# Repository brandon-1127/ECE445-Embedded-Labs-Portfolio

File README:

Hello!

This is a portfolio of all my embedded labs for ECE445 at UT Austin. They range from speakers to alarm clocks to my final project(a glove controlled wirless robotic arm).

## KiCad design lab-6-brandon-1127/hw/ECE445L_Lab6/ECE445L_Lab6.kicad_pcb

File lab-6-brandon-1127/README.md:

## 0 Repository Structure

The typical explanation for the repo structure. Lab specific instructions can be
found further below.

### 0.1 HW

The `hw` folder should contain your schematic and board files for your PCB or
circuits. In labs 1-5 and 10, you will be creating schematics for your circuit
in KiCad.

### 0.2 SW

The `sw` folder should contain your application firmware and software written
for the lab. The `sw/inc` folder contains firmware drivers written for you by
Professor Valvano. Feel free to write your own (in fact, in some labs, you may
be required to write your own).

You can place any other source files in the `sw` folder. TAs will look at the
files you create and/or modify for software quality and for running your
project.

### 0.3 Resources

A couple files are provided in the Resources folder so you don't have to keep
searching for that one TI document. Some of them are immediately useful, like
the TM4C datasheet. Others may be useful for your final project, like the
TM4C_System_Design_Guidelines page.

### 0.4 Git and Github

We will extensively use Git and Github for managing lab projects. This makes it
easier for TAs to grade and help debug the project by allowing us to see commit
histories, maintain a common project structure, and likewise, it makes it easier
for students to collaborate with partners, merge different codebases, and to
debug their work by having a history of commits.

Two common ways of using Git and Github are [Github Desktop](https://desktop.github.com/) and the [command line](https://git-scm.com/downloads).
[Tutorials](https://dev.to/mollynem/git-github--workflow-fundamentals-5496) are also abundant on the net for you to peruse. We've provided a cheatsheet for git
in the Resources folder.

It is highly recommended to make the most out of Git, even if you've never used
it before. Version control will save you a lot of suffering, and tools like Git
or SVN are ubiquitous in the industry.

A gitignore file is added to the root of this repo that may prevent specific
files from being tagged to the repo. This are typically autogenerated output
files we don't care about, but sometimes other stuff (like .lib files) falls
through that we want. Feel free to modify if necessary.

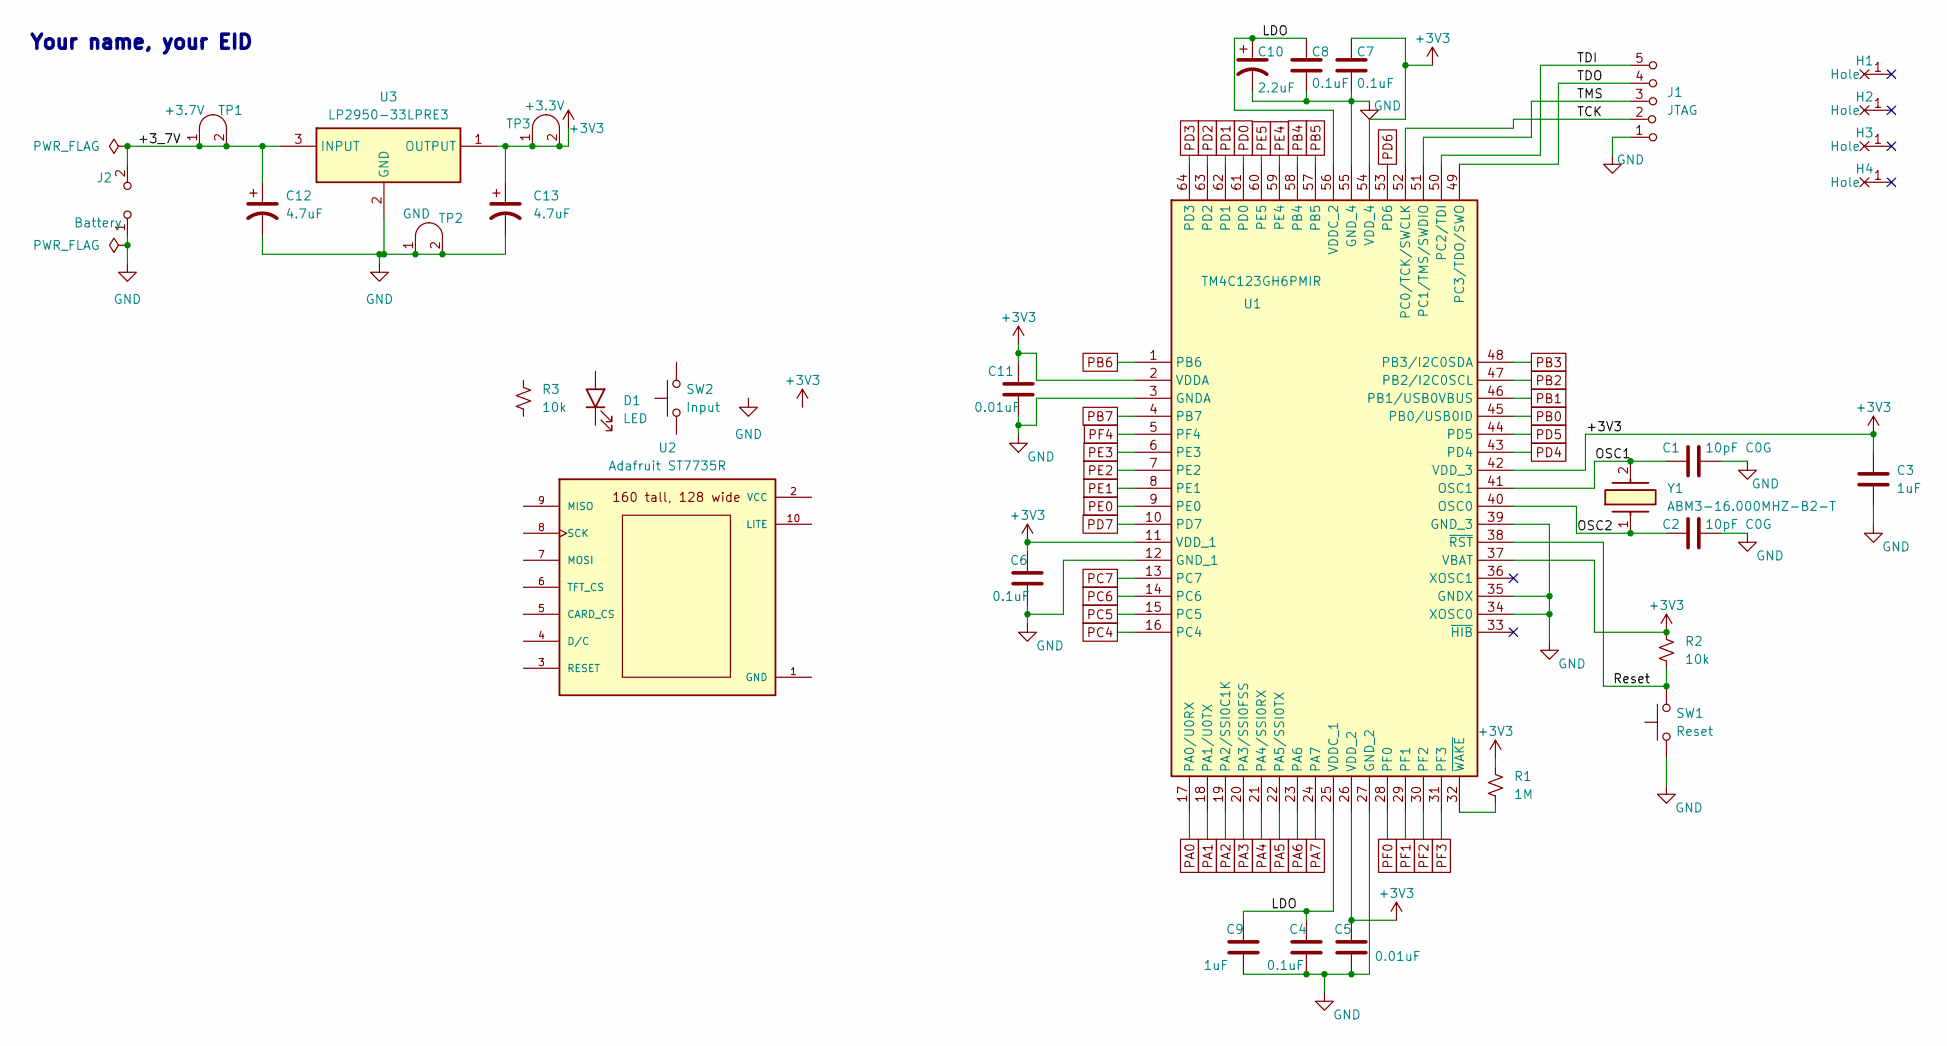
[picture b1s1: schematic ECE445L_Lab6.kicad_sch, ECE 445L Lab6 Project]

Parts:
C1, C2: 10pF C0G; C_Axial_200mil
C3, C9: 1uF; C_Axial_200mil
C4, C6, C7, C8: 0.1uF; C_Axial_200mil
C5, C11: 0.01uF; C_Axial_200mil
C10: 2.2uF; CP_Radial_Tantal200mil
C12, C13: 4.7uF; CP_Radial_Tantal200mil
D1: LED; LED_D5.0mm
H1, H2, H3, H4: MountingHole_4_40
J1: JTAG; PinHeader_1x05_P2.54mm_Vertical
J2: Battery; PinHeader_1x02_P2.54mm_Vertical
R1: 1M; R_Axial_DIN0204_L3.6mm_D1.6mm_P7.62mm_Horizontal
R2, R3: 10k; R_Axial_DIN0204_L3.6mm_D1.6mm_P7.62mm_Horizontal
SW1: Reset; SW_PUSH_6mm
SW2: Input; SW_PUSH_6mm
TP1: +3.7V; Testpoint_1x02_P2.54mm
TP2: GND; Testpoint_1x02_P2.54mm
TP3: +3.3V; Testpoint_1x02_P2.54mm
U1: TM4C123GH6PMIR; QFP50P1200X1200X160-64N; Mouser Part Number 595-TM4C123GH6PMIR
U2: Adafruit ST7735R; adafruit_st7735r2
U3: LP2950-33LPRE3; TL431CLPM; Mouser Part Number 595-LP2950-33LPRE3
Y1: ABM3-16.000MHZ-B2-T; ABM3; Mouser Part Number 815-ABM3-16-B2-T

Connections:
+3V3: C3.1, C5.1, C6.1, C7.1, C11.1, C13.1, R1.1, R2.1, TP3.1 (A), TP3.2 (B), U1.2 (VDDA), U1.11 (VDD_1), U1.26 (VDD_2), U1.37 (VBAT), U1.42 (VDD_3), U1.54 (VDD_4), U3.1 (OUTPUT)
/+3_7V: C12.1, J2.2 (B), TP1.1 (A), TP1.2 (B), U3.3 (INPUT)
/LDO: C4.1, C8.1, C9.1, C10.1, U1.25 (VDDC_1), U1.56 (VDDC_2)
/OSC1: C1.1, U1.41 (OSC1), Y1.2
/OSC2: C2.1, U1.40 (OSC0), Y1.1
/Reset: R2.2, SW1.2, U1.38 (~RST)
/TCK: J1.2 (B), U1.52 (PC0/TCK/SWCLK)
/TDI: J1.5 (C), U1.50 (PC2/TDI)
/TDO: J1.4 (C), U1.49 (PC3/TDO/SWO)
/TMS: J1.3 (C), U1.51 (PC1/TMS/SWDIO)
GND: C1.2, C2.2, C3.2, C4.2, C5.2, C6.2, C7.2, C8.2, C9.2, C10.2, C11.2, C12.2, C13.2, J1.1 (A), J2.1 (A), SW1.1, TP2.1 (A), TP2.2 (B), U1.3 (GNDA), U1.12 (GND_1), U1.27 (GND_2), U1.34 (XOSC0), U1.35 (GNDX), U1.39 (GND_3), U1.55 (GND_4), U3.2 (GND)
unnamed: R1.2, U1.32 (~WAKE)
PA0: U1.17 (PA0/U0RX)
PA1: U1.18 (PA1/U0TX)
PA2: U1.19 (PA2/SSI0C1K)
PA3: U1.20 (PA3/SSI0FSS)
PA4: U1.21 (PA4/SSI0RX)
PA5: U1.22 (PA5/SSI0TX)
PA6: U1.23 (PA6)
PA7: U1.24 (PA7)
PB0: U1.45 (PB0/USB0ID)
PB1: U1.46 (PB1/USB0VBUS)
PB2: U1.47 (PB2/I2C0SCL)
PB3: U1.48 (PB3/I2C0SDA)
PB4: U1.58 (PB4)
PB5: U1.57 (PB5)
PB6: U1.1 (PB6)
PB7: U1.4 (PB7)
PC4: U1.16 (PC4)
PC5: U1.15 (PC5)
PC6: U1.14 (PC6)
PC7: U1.13 (PC7)
PD0: U1.61 (PD0)
PD1: U1.62 (PD1)
PD2: U1.63 (PD2)
PD3: U1.64 (PD3)
PD4: U1.43 (PD4)
PD5: U1.44 (PD5)
PD6: U1.53 (PD6)
PD7: U1.10 (PD7)
PE0: U1.9 (PE0)
PE1: U1.8 (PE1)
PE2: U1.7 (PE2)
PE3: U1.6 (PE3)
PE4: U1.59 (PE4)
PE5: U1.60 (PE5)
PF0: U1.28 (PF0)
PF1: U1.29 (PF1)
PF2: U1.30 (PF2)
PF3: U1.31 (PF3)
PF4: U1.5 (PF4)

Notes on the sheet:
Your name, your EID

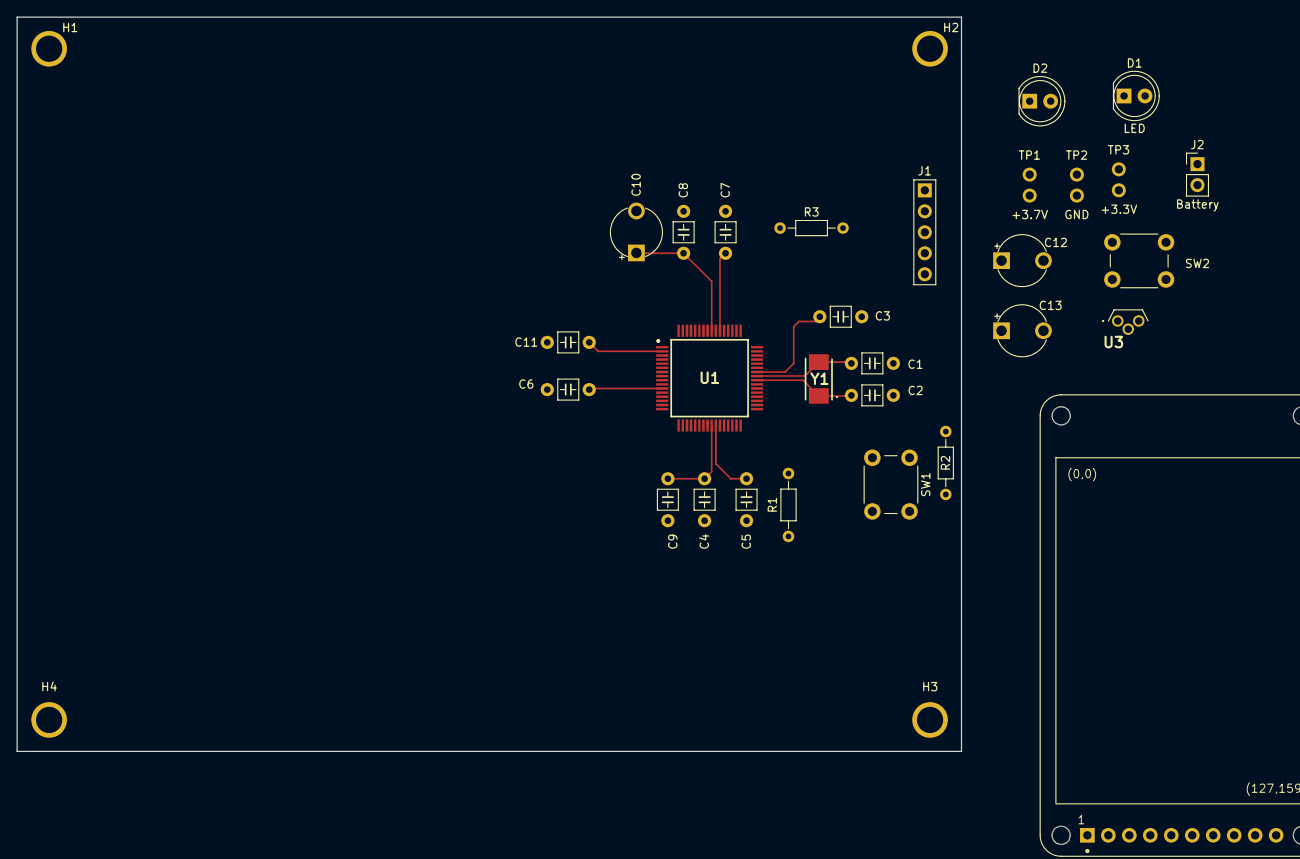
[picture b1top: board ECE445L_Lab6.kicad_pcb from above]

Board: 2 copper layers, 114.4 x 88.9 mm, 33 parts (0 on the bottom side), 12 nets.

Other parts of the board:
D2: LED; LED_D5.0mm

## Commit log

2026-02-28 Consolidate all embedded labs into one repo
2026-02-28 removed lab 6 cause not done
